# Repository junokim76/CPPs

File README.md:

<html>
    <head>
        <meta charset="UTF-8">
    </head>
    <body>
        <h1>Cursos - IFSC<h1>
        <p> TECNICO DES. SISTEMAS do IFSC 2022/2023 </p>
        <p> TECNICO ELETRONICA do IFSC 2024 </p>
        <p> ENG ELETRONICA do IFSC 2024 </p>
    </body>
</html>

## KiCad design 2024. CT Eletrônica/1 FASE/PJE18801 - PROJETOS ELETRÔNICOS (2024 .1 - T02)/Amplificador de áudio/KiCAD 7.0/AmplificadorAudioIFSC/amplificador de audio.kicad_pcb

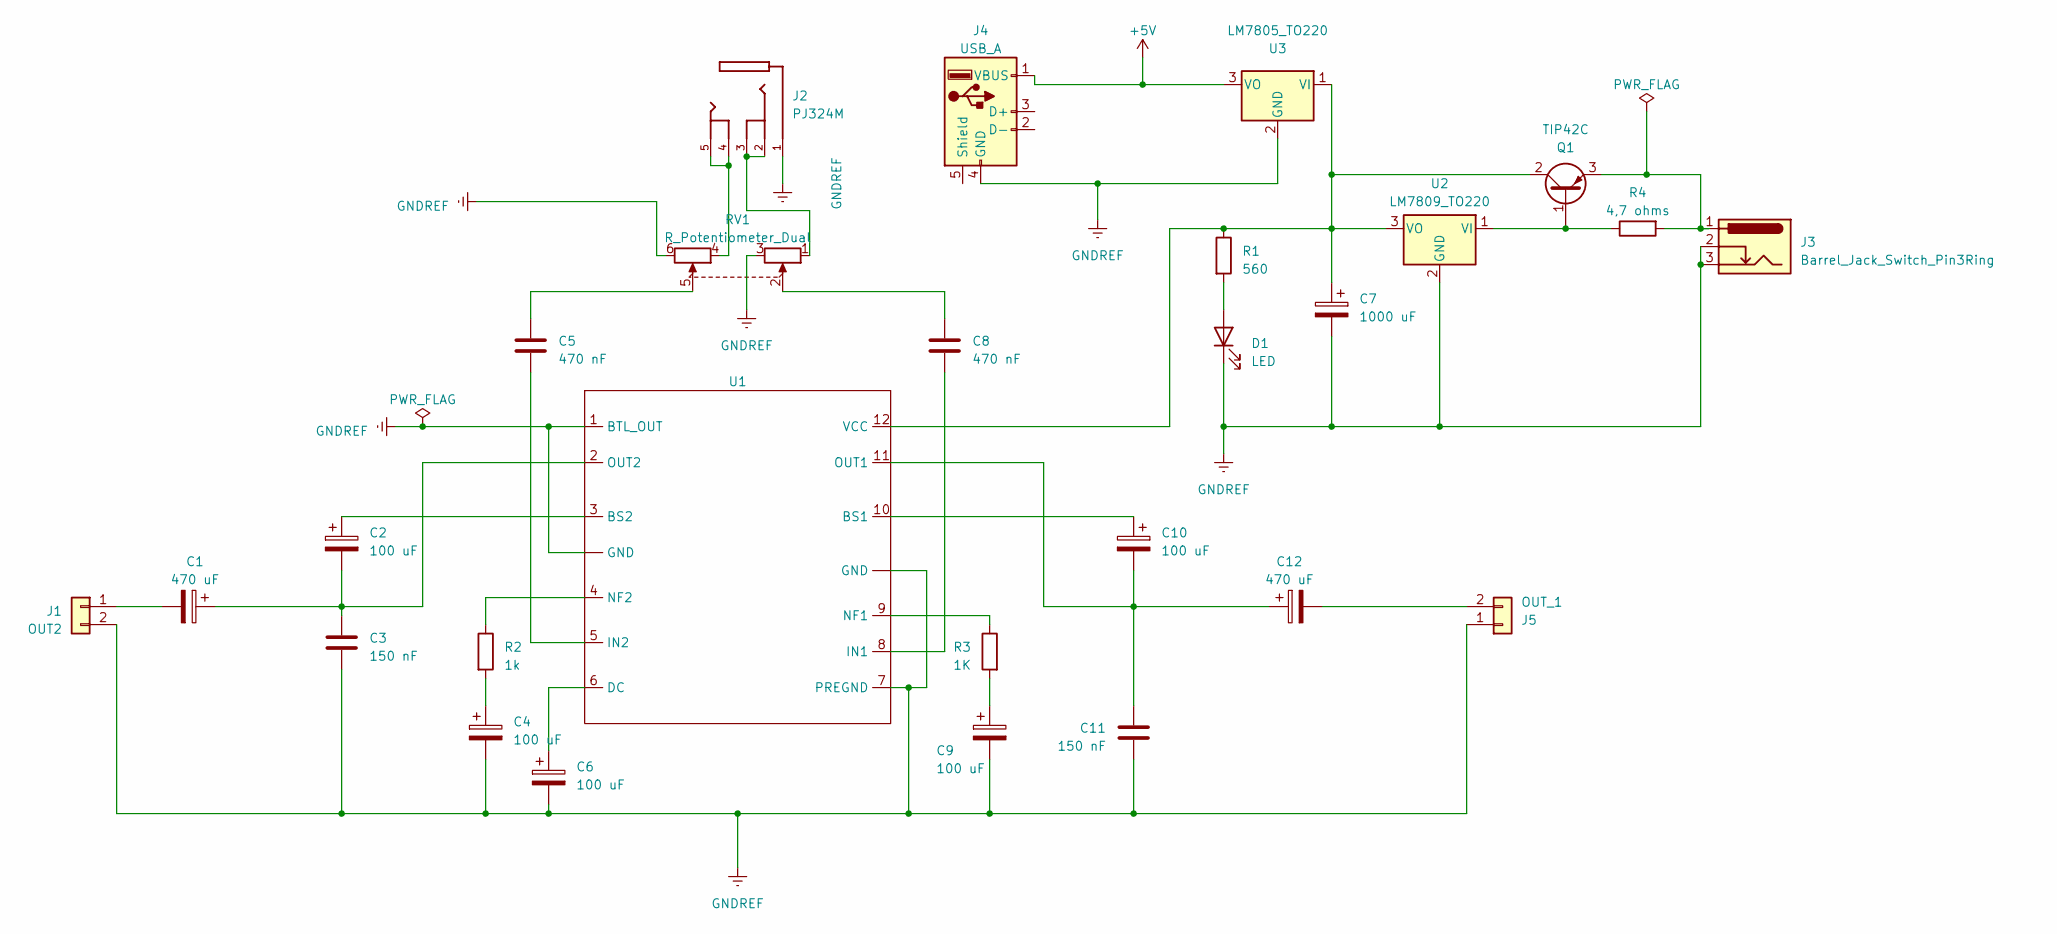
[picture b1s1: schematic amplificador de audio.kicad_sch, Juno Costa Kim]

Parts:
C1, C12: 470 uF; CP_Radial_D8.0mm_P3.50mm
C2, C4, C6, C9, C10: 100 uF; CP_Radial_D6.3mm_P2.50mm
C3, C11: 150 nF; C_Rect_L7.2mm_W5.5mm_P5.00mm_FKS2_FKP2_MKS2_MKP2
C5, C8: 470 nF; C_Rect_L16.5mm_W4.7mm_P15.00mm_MKT
C7: 1000 uF; CP_Radial_D10.0mm_P5.00mm
D1: LED; LED_D5.0mm
J1: OUT2; TerminalBlock_bornier-2_P5.08mm
J2: PJ324M; WENZHOU_PJ324M; PARTREV N/A
J3: Barrel_Jack_Switch_Pin3Ring; BarrelJack_CUI_PJ-102AH_Horizontal
J4: USB_A; USB_A_Stewart_SS-52100-001_Horizontal
J5: OUT_1; TerminalBlock_bornier-2_P5.08mm
Q1: TIP42C; TO-220-3_Vertical
R1: 560; R_Axial_DIN0207_L6.3mm_D2.5mm_P7.62mm_Horizontal
R2: 1k; R_Axial_DIN0207_L6.3mm_D2.5mm_P7.62mm_Horizontal
R3: 1K; R_Axial_DIN0207_L6.3mm_D2.5mm_P7.62mm_Horizontal
R4: 4,7 ohms; R_Axial_DIN0207_L6.3mm_D2.5mm_P7.62mm_Horizontal
RV1: R_Potentiometer_Dual; Potentiometer_Piher_PC-16_Dual_Horizontal
U1: DIP-16_W7.62mm
U2: LM7809_TO220; TO-220-3_Vertical
U3: LM7805_TO220; TO-220-3_Vertical

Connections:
+5V: J4.1 (VBUS), U3.3 (VO)
GNDREF: C3.2, C4.2, C6.2, C7.2, C9.2, C11.2, D1.1 (K), J1.2, J2.1, J3.2, J3.3, J4.4 (GND), J5.1, RV1.3, RV1.6, U1. (GND), U1.1 (BTL_OUT), U1.7 (PREGND), U1.GND, U2.2 (GND), U3.2 (GND)
unnamed: C4.1, R2.2
unnamed: C5.1, RV1.5
unnamed: C8.1, RV1.2
unnamed: C9.1, R3.2
unnamed: D1.2 (A), R1.2
unnamed: C1.2, J1.1
unnamed: J2.2, J2.3, RV1.1
unnamed: J2.4, J2.5, RV1.4
unnamed: C12.2, J5.2
unnamed: Q1.1 (B), R4.1, U2.1 (VI)
unnamed: C7.1, Q1.2 (C), R1.1, U1.12 (VCC), U2.3 (VO), U3.1 (VI)
unnamed: J3.1, Q1.3 (E), R4.2
unnamed: C10.1, U1.10 (BS1)
unnamed: C2.1, U1.3 (BS2)
unnamed: C6.1, U1.6 (DC)
unnamed: C8.2, U1.8 (IN1)
unnamed: C5.2, U1.5 (IN2)
unnamed: R3.1, U1.9 (NF1)
unnamed: R2.1, U1.4 (NF2)
unnamed: C10.2, C11.1, C12.1, U1.11 (OUT1)
unnamed: C1.1, C2.2, C3.1, U1.2 (OUT2)

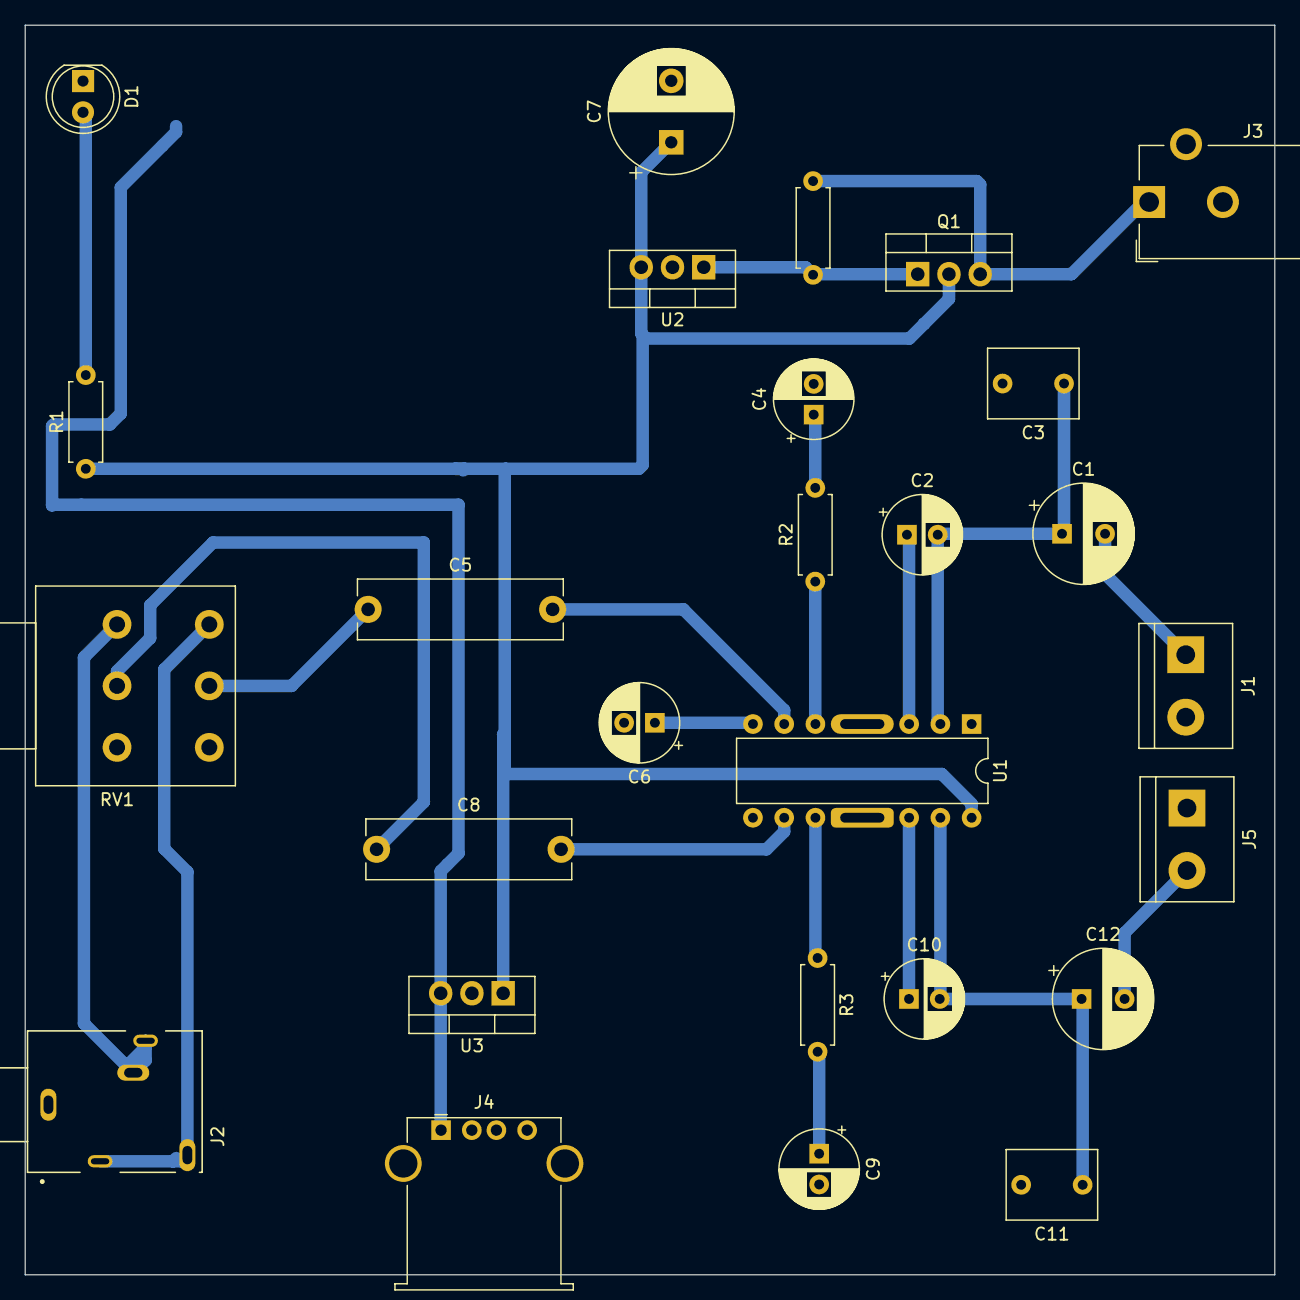
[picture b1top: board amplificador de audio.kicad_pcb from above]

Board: 2 copper layers, 101.6 x 101.6 mm, 27 parts (0 on the bottom side), 23 nets.

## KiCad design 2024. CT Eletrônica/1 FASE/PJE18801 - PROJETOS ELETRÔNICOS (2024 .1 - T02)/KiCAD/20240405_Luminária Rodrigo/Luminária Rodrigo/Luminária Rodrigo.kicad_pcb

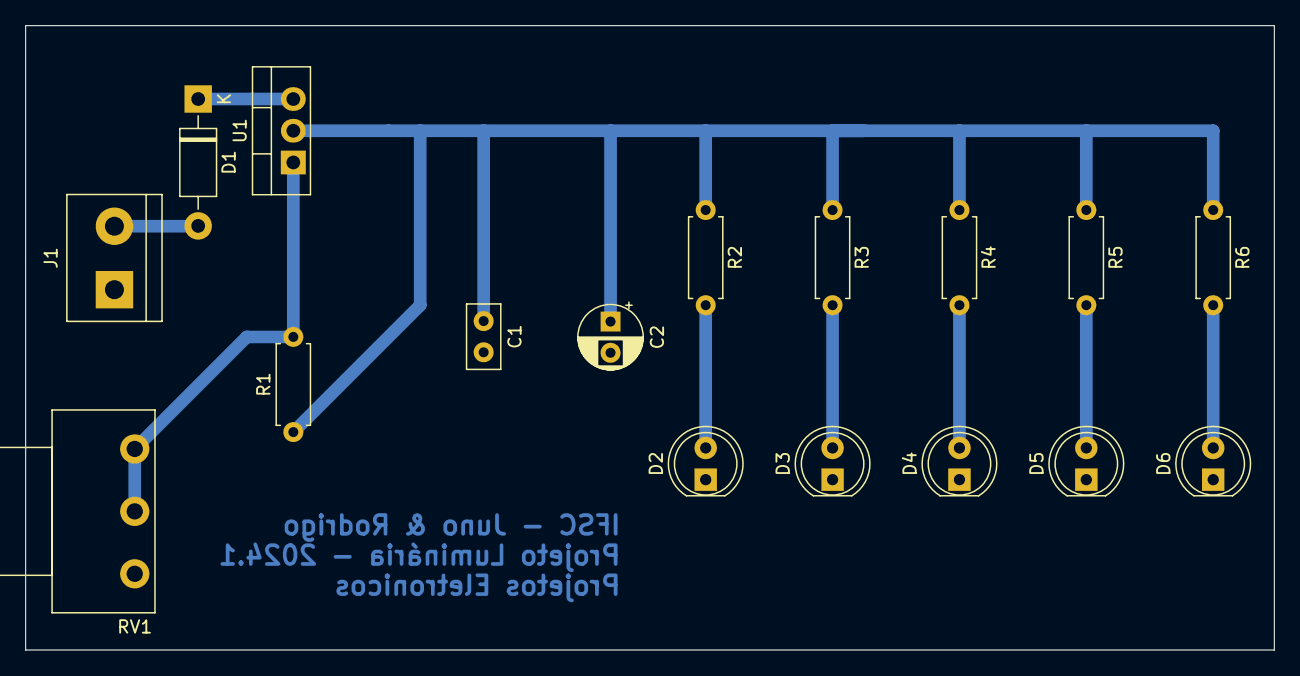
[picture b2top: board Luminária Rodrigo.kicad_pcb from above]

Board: 2 copper layers, 100.0 x 50.0 mm, 17 parts (0 on the bottom side), 10 nets.

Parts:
C1: 100nF; C_Disc_D5.0mm_W2.5mm_P2.50mm
C2: 10uF; CP_Radial_D5.0mm_P2.50mm
D1: 1N4007; D_DO-41_SOD81_P10.16mm_Horizontal
D2, D3, D4, D5, D6: LED; LED_D5.0mm
J1: Conn_01x02; TerminalBlock_bornier-2_P5.08mm
R1: 220; R_Axial_DIN0207_L6.3mm_D2.5mm_P7.62mm_Horizontal
R2, R3, R4, R5, R6: 330; R_Axial_DIN0207_L6.3mm_D2.5mm_P7.62mm_Horizontal
RV1: 2k; Potentiometer_Piher_PC-16_Single_Horizontal
U1: LM317_TO-220; TO-220-3_Vertical

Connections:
GNDREF: C1.2, C2.2, D2.1 (K), D3.1 (K), D4.1 (K), D5.1 (K), D6.1 (K), J1.1, RV1.3
unnamed: D1.2 (A), J1.2
unnamed: D1.1 (K), U1.3 (VI)
unnamed: D2.2 (A), R2.2
unnamed: D3.2 (A), R3.2
unnamed: D4.2 (A), R4.2
unnamed: D5.2 (A), R5.2
unnamed: D6.2 (A), R6.2
unnamed: R1.2, RV1.1, RV1.2, U1.1 (ADJ)
unnamed: C1.1, C2.1, R1.1, R2.1, R3.1, R4.1, R5.1, R6.1, U1.2 (VO)

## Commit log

2022-07-30 Atividade de Geometria Plana em C++
    Atividade de Geometria Plana em C++
    IFSC LPO 1
2022-07-30 Calcula Salario Horas Extras e Deduções
    Calcula Salario Horas Extras e Deduções
    IFSC - LPO1 - Trabalho 1
2022-07-30 Corrige Prova de Multipla Escolha
    IFSC - LPO 1
    Desenvolver um programa para realizar a correção de um prova de múltipla escolha.
    Os dados iniciais a serem lidos são:
    - A quantidade de candidatos (N) e
    - A quantidade de questões aplicadas (M).
    As respostas possíveis que poderão ser aceitas são: A, B, C, D e E.
2022-12-17 Rename LPO1-Atividadade12_GeometriaPalna_Juno.cpp to LPO1-GeometriaPalna.cpp
2022-12-17 Reorganizando Diretório GITHub
    Juno Kim
    Reorganizando diretórios IFSC CTDS 2022
2022-12-17 Geometria Plana
    Juno Kim
    Geometria Plana - Cálculo do Quadradro, Triângula e Circunferência
2022-12-17 Geometria Plana - Cálculo do Quadrado, Triângulo e Circunferência
2022-12-17 Cálculo Salário Valor Hora com deduções INSS e IR
2022-12-17 Cálculo Salário por Valor Hora e Deduções de INSS e IR
2022-12-17 Corrige Prova de Múltipla Escolha
2022-12-17 README.md
2022-12-17 Corrige Prova Múltipla Escolha
2022-12-17 Geometria Plana - Cálculo do Quadrado, Triângulo e Circunferência
2023-03-08 Adicionando nova UC GEM I
2023-03-08 UC IHC
2023-03-08 UC LPO I
2023-03-08 Alteração de nome UC IHC
2023-03-08 UC PRS I
2023-03-08 UC FIN
2023-03-08 UC BDII
2023-03-08 OC PRW
2023-03-08 UC PRW
2023-03-08 UC SWE
2023-03-08 UC PRS II
2023-03-15 POO UPDATE
2025-01-12 Acertando as estruturas de diretorio
2025-01-12 Add CT Eletrônica
2025-01-12 Add Eng Eletronica
2025-01-12 Change names
